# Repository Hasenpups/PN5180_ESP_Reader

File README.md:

[![CC BY-NC-SA 4.0][cc-by-nc-sa-shield]][cc-by-nc-sa]

This work is licensed under a
[Creative Commons Attribution-NonCommercial-ShareAlike 4.0 International License][cc-by-nc-sa].

[![CC BY-NC-SA 4.0][cc-by-nc-sa-image]][cc-by-nc-sa]

[cc-by-nc-sa]: http://creativecommons.org/licenses/by-nc-sa/4.0/
[cc-by-nc-sa-image]: https://licensebuttons.net/l/by-nc-sa/4.0/88x31.png
[cc-by-nc-sa-shield]: https://img.shields.io/badge/License-CC%20BY--NC--SA%204.0-lightgrey.svg

## Donations / Spenden
If somebody wants to support me for upcoming projects :)  
- PayPal:  
- Amazon Giftcard: https://www.amazon.de/Amazon-Gutschein-per-E-Mail-Amazon/dp/B0054PDOV8 - stefan.riese@me.com

# PN5180 ESP reader
This reader uses a PN5180 RFID reader and a Wemos D1 mini to read RFID tags like ISO 15693.

# Used hardware
- 1 x PN5180 reader (https://www.amazon.de/dp/B0BFGWS7MZ)
- 1 x Wemos D1 mini (https://www.amazon.de/AZDelivery-NodeMCU-ESP8266EX-kompatibel-inklusive/dp/B08BTYHJM1)
- 1 x 10x3mm magnet (https://www.amazon.de/Temporaryt-Neodym-Magnete-Aufbewahrungs-K%C3%BChlschrank/dp/B07DNBXBWQ)
- 4 x M3x6 screw

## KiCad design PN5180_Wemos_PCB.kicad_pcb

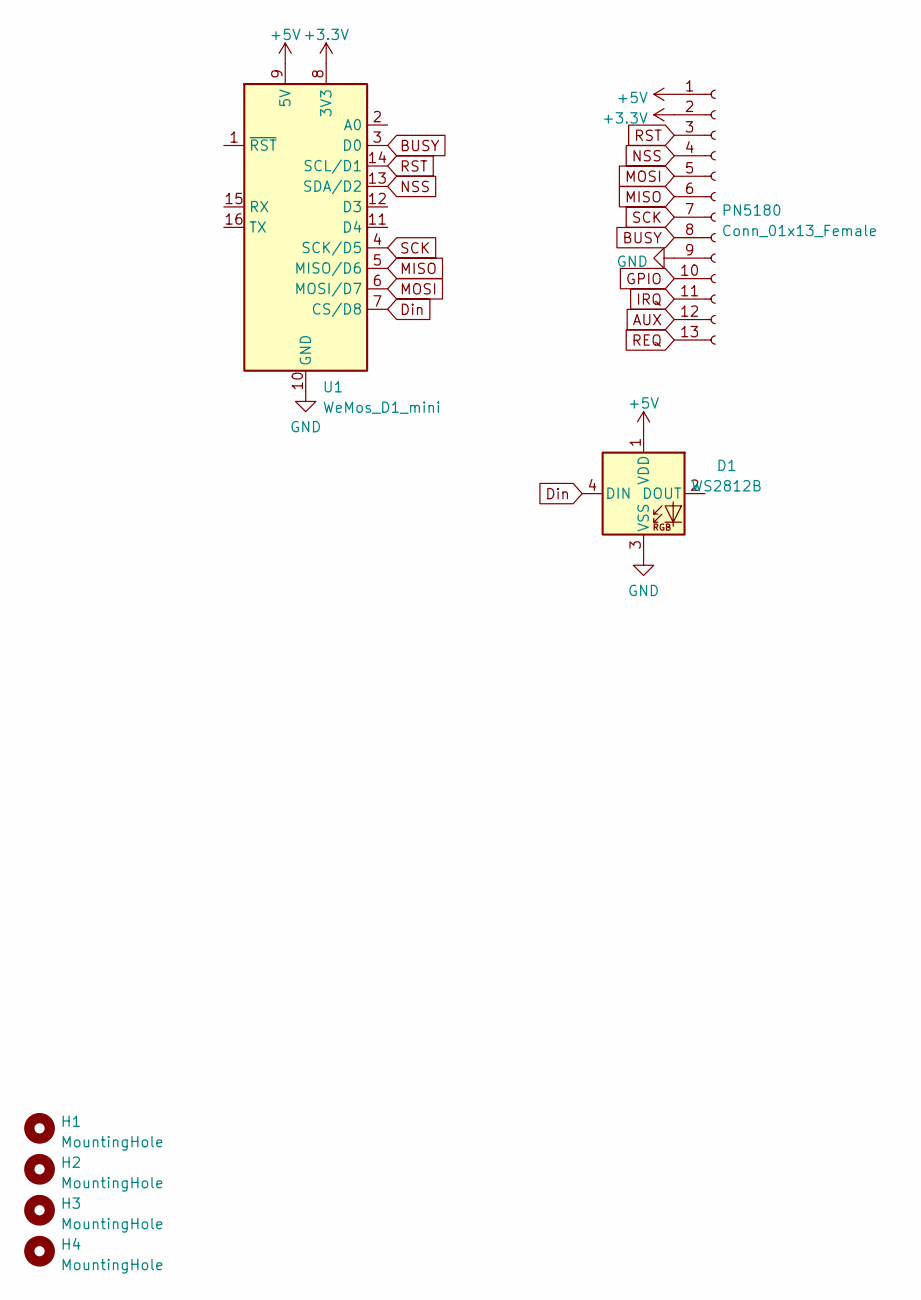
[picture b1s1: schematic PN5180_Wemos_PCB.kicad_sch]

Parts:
D1: WS2812B; LED_WS2812B_PLCC4_5.0x5.0mm_P3.2mm
H1, H2, H3, H4: MountingHole; MountingHole_3.2mm_M3_DIN965_Pad
PN5180: Conn_01x13_Female; PinHeader_1x13_P2.54mm_Vertical
U1: WeMos_D1_mini; WEMOS_D1_mini_light

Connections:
+3.3V: PN5180.2, U1.8 (3V3)
+5V: D1.1 (VDD), PN5180.1, U1.9 (5V)
AUX: PN5180.12
BUSY: PN5180.8, U1.3 (D0)
Din: D1.4 (DIN), U1.7 (CS/D8)
GND: D1.3 (VSS), PN5180.9, U1.10 (GND)
GPIO: PN5180.10
IRQ: PN5180.11
MISO: PN5180.6, U1.5 (MISO/D6)
MOSI: PN5180.5, U1.6 (MOSI/D7)
NSS: PN5180.4, U1.13 (SDA/D2)
REQ: PN5180.13
RST: PN5180.3, U1.14 (SCL/D1)
SCK: PN5180.7, U1.4 (SCK/D5)

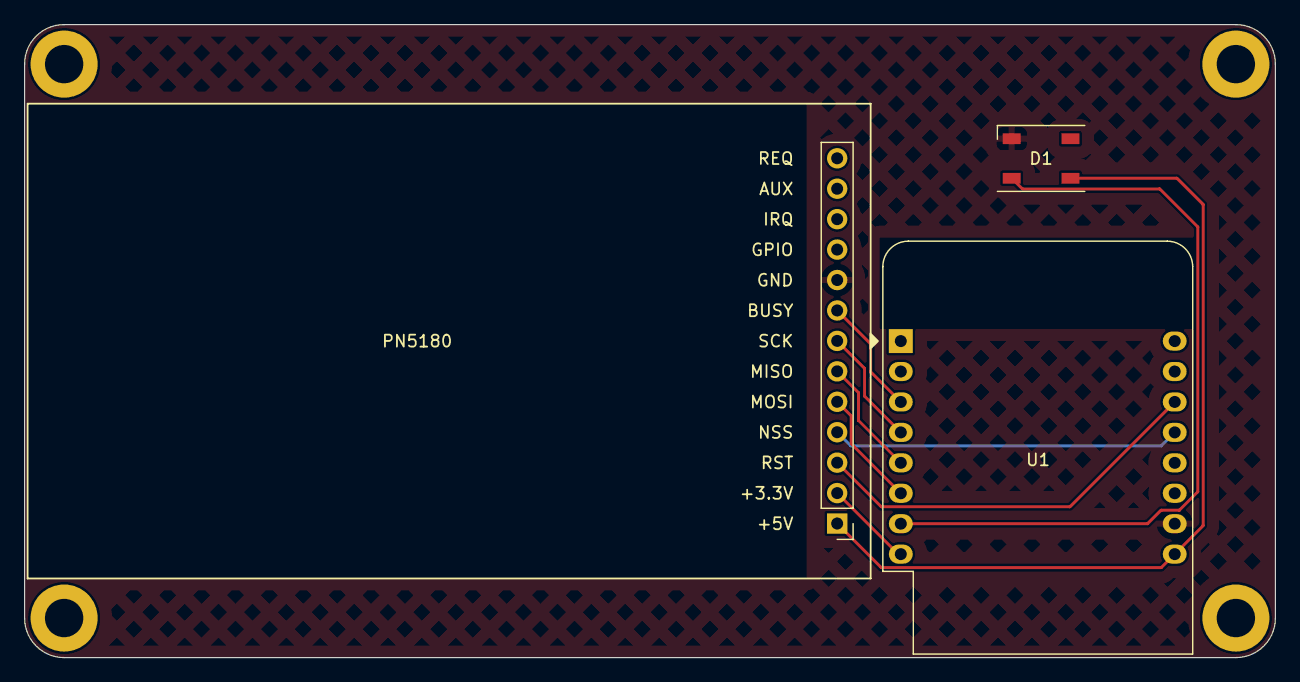
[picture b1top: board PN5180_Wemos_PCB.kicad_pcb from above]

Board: 2 copper layers, 104.4 x 52.8 mm, 7 parts (0 on the bottom side), 10 nets.

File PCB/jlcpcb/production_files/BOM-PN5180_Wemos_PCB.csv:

Comment,Designator,Footprint,LCSC
WS2812B,D1,LED_WS2812B_PLCC4_5.0x5.0mm_P3.2mm,
MountingHole,H3,MountingHole_3.2mm_M3_DIN965_Pad,
MountingHole,H2,MountingHole_3.2mm_M3_DIN965_Pad,
MountingHole,H1,MountingHole_3.2mm_M3_DIN965_Pad,
Conn_01x13_Female,PN5180,PinHeader_1x13_P2.54mm_Vertical,
WeMos_D1_mini,U1,WEMOS_D1_mini_light,
MountingHole,H4,MountingHole_3.2mm_M3_DIN965_Pad,

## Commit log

2023-02-13 - initial commit
2023-02-13 Add files via upload
    - add rendering and PDF
2023-02-15 - restructure files
2023-02-15 - add images
2023-03-01 - cleanup
